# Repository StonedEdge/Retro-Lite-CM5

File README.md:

<div align="center">
  <h1>Retro Lite/RetrOLED CM5: RK3588s Gaming Handheld</h1>
</div>

<div align="center">
  
</div>
<p align="center">This is the RetroLED CM5, a handheld console designed by GinKage, notime2d8 and StonedEdge.</p>

<div align="center">
  
</div>
<p align="center">Running Hollow Knight via Box64 and Steam on upstream Armbian kernel.</p>

<div align="center">
  
</div>
<p align="center">Official Android support, thanks to the work of notime2d8.</p>

<div align="center">
  
</div>
<p align="center">Latest ROCKNIX images available with Vulkan driver support.</p>

<div align="center">
  
</div>
<p align="center">Open source hardware files available for download.</p>

The Retro Lite/RetrOLED CM5 is an upgrade to the Retro Lite CM4 handheld. The project goal is to create a more powerful handheld that can handle 3DS, PS2 and GC emulation (none of which the Pi can do). I also would like to be able to play some games via Box64/86. It has a relatively large battery so run time should be excellent, considering it is ARM based. **Now with an optional OLED upgrade!**

Powered by the RK3588s compute module from Radxa, which is an SBC SOM module with an ARMv8 64-bit processor. Features 8 cores/threads - 4 x ARM Cortex-A55/A76 cores with A55 cores clocked at 1.8GHz, and A76 cores clocked at 2.4GHz. It also has a built-in Mali G610 GPU. 

The Retro Lite/RetrOLED CM5 offers a more modern gaming experience with DisplayPort via USB Type-C, USB 3.0 & HDMI 2.1. Built-in PCIe WiFI 6.0 & BT 5.2, as well as a new 720p IPS display @ 5.5" with touchscreen support & dual tact trigger buttons for GameCube support, make this a much more viable low-powered ARM SBC gaming PC than the Raspberry Pi 4. 

The operating system will be based on Armbian, with a custom device tree for hardware interfacing & RetroPie pre-installed. However, the user can use it however they would like, either in a Linux desktop environment or with other Linux based frontends, such as ES-DE. This handheld should be able to play the entire PS2 library at least 1x native resolution for all games, as well as GameCube at 1x on Linux with OpenGLES drivers. Android is currently more performant due to Vulkan drivers, however Linux Vulkan blobs should come soon (or someday, who knows). We also now have succesfully compiled ROCKNIX as well. Eventually I will compile all of the final images to GitHub. 

For regular updates/following progress on the build, please check out the forum post here:
https://bitbuilt.net/forums/index.php?threads/retro-lite-cm5.5815/

# Retro Lite/RetrOLED CM5: Radxa RK3588s Handheld 

## Features

Hardware specifications:

- 3D printable housing in PLA. Comfort grips for added ergonomics
- Radxa CM5 Compute Module (8GB RAM/64GB eMMC)
- SoC – Rockchip RK3588S octa-core processor with 4x Cortex‑A76 cores @ up to 2.4GHz, 4x Cortex‑A55 core @ 1.8GHz
Arm Mali-G610 MP4 “Odin” GPU Video decoder – 8Kp60 H.265, VP9, AVS2, 8Kp30 H.264 AVC/MVC, 4Kp60 AV1, 1080p60 MPEG-2/-1, VC-1, VP8 Video encoder – 8Kp30 H.265/H.264 video encoder
- WiFi 6/Bluetooth 5.2 via PCIe E-key slot (Intel AX210) - https://www.intel.com/content/www/us/en/products/sku/204836/intel-wifi-6e-ax210-gig/specifications.html
- 6 layer carrier board with 3 B2B mezzanine connectors to interface with any Radxa CM5 module 
- 5v boost rated at 3.5A continuous current
- RP2040 gamepad - complete with SDL mappings and evdev gyro support/mouse control via MPU6050
- 1280 x 720p (5.5" DSI IPS LCD): DSI video output on internal display
**- New: Optional 1920 x 1080p (5.44" AMOLED): DSI video output on internal display** 
- Up to 4k HDMI video output via HDMI output
- Up to 4k DisplayPort Alternate Mode via Type-C
- USB 2.0/3.1 capable USB-C data transfer
- USB-C dual role port functionality (sink/source)
- Brightness and volume HUD adjustment. Brightness is adjusted by holding plus hotkey + down/up. Volume controlled either by volume buttons or plus hotkey + left right DPAD
- USB-C PD charging support via sink profiles supporting 5V/3A, 9V/3A, 12V/2A & 15V/2.6A (switch charger) via TPS65987D PD controller (see binary in TPS65987D folder). Recommended to use <12V for best charge and play performance 
- Stereo Audio Output via i2s. Dual stereo speakers with ported chambers
- Headphone jack, with automatic switching
- 5000mAh lipo, providing around 1.5-5 hours of gameplay depending on load (to be upgraded soon to >8000mAh)
- Dual stacked shoulder buttons (L, R, LZ, RZ) with dual tact buttons for GameCube functionality (LR analog/LR digital)
- 2x hall effect analog sticks running at 3v3
- Resin casted ABXY, DPAD, start+select, shoulder buttons
- Silicone membranes for nice button feel 

Software specifications:

- Armbian GNOME desktop (Kernel 6.1.57 as of this post)
- Android 13 support (beta)
- Full upstream Rocknix support
- Wayland windowing system (xorg capable)
- Hardware graphics support via Panfrost/OpenGLES/I want a broken vulkan driver "support"
- Safe software/hardware shutdown (either from software or via button)
- Low power sleep mode - in my tests, 24 hours in standby mode draws around 6% of total battery life
- Range adjustable joysticks in software by pressing plus hotkey plus R3 --> A --> rotate sticks --> A combination
-------------------------------------------------------------------------------------------------------

### CAD
Enclosure files have been uploaded in STL and STEP format [here.](https://github.com/StonedEdge/Retro-Lite-CM5/tree/main/enclosure)
Make sure to use v2 as these contain all the latest and greatest changes. 

-------------------------------------------------------------------------------------------------------

### PCB
v1 Controller PCBs have been uploaded [here.](https://github.com/StonedEdge/Retro-Lite-CM5/tree/main/rp2040_gamepad/PCB)
Please note that you will not be able to assemble the unit with the UART/serial debug components soldered onto the boards, so make sure these aren't populated. 

v1.1 CM5 carrier boards have been uploaded [here.](https://github.com/StonedEdge/Retro-Lite-CM5/tree/main/cm5_carrier_pcb)

-------------------------------------------------------------------------------------------------------

### BOM (Bill of Materials) 
v1 Right Controller PCB BOM have been uploaded [here.](https://github.com/StonedEdge/Retro-Lite-CM5/blob/main/rp2040_gamepad/PCB/Retro_Lite_CM5_Right_PCB_v1%20-%20BOM.csv)

v1 Left Controller PCB BOM have been uploaded [here.](https://github.com/StonedEdge/Retro-Lite-CM5/blob/main/rp2040_gamepad/PCB/v1/Retro_Lite_CM5_Left_PCB_v1%20-%20BOM.csv)

v1 V2.2 Carrier PCB BOM has been uploaded [here.](https://github.com/StonedEdge/Retro-Lite-CM5/blob/main/cm5_carrier_pcb/Retro_Lite_CM5_IO_X2.2_BOM.csv) 
The board has been verified and fully functional with Radxa V2.2 CM5 modules! V2.21 also works fine. 

-------------------------------------------------------------------------------------------------------

### To-do
- [x] Hardware familiarization - Orange Pi 5/Radxa CM5/IO board schematics
- [x] Design v1 prototype left/right controller PCBs (ATMEGA32u4 based)
- [x] Design v1 DSI test display board
- [x] Design v1 Power Management/DisplayPort/USB-C PD test board
- [x] Order v1 Power Management/DisplayPort/USB-C PD test board
- [x] Design v2 prototype left/right controller PCBs (RP2040 based)
- [x] Test v1 Power Management/DisplayPort Alternate Mode/USB-C PD test board functionality - works!
- [x] Design CM5 carrier main board (v1.0) that implements new hardware features, such as DisplayPort, USB3 and PCIe
- [x] Order CM5 carrier board (v1.0) with desired fab house. (It's in production!)
- [x] Test CM5 carrier board (v1.0) hardware for a basic functioning prototype
- [x] Redesign CM5 carrier board (v1.1) with fixes for 3rd connector polarity & other small fixes
- [x] Reorder v1.1 carrier board
- [x] Investigate RK806 PMIC issue
- [x] Prepare an Armbian based OS image, including the BSP (bootloader, dtb and kernel) for the RK3588s Armbian rootfs. DTB should include the ILI9881C/WM8960 drivers
- [x] Integrate new 5.5 inch MIPI DSI display. This includes enabling the ILI9881C display driver, device tree customizations for the display
- [x] Test and verify display functionality, including proper backlight & 60 FPS. Verify display works with Armbian 
- [x] WM8960 codec integration via Orange Pi 5/CM5 IO for testing. Integrate the WM8960 i2c code driver including any device tree customizations for codec. Finally, test and verify audio works correctly
- [x] Integrate touch/verify via the GT911 controller 
- [x] Test and verify emulators work correctly with Mali blobs and can be launched via EmulationStation front end
- [x] Setup Mali Open GL blob drivers to work with PS2 (AetherSX2) & GC (Dolphin) emulators due to no Vulkan backend available (yet!)
- [x] Write HID controller code for RP2040. Verify basic gamepad functionality works as intended
- [x] Integrate an IMU into the controller PCB for gyro functionality. Include EKF algorithm (MPU-6050 6-axis IMU) 
- [x] Redesign housing (increase 3mm in all directions) in Solidworks. Improve trigger feel and add battery mounting bracket
- [x] Redesign housing v2 (increase thickness to accomodate 6Ah battery cell at 3.8v, mount battery and fan to front housing)
- [x] Redesign housing with injection molding in mind - include appropriate draft angles, ribs, gussets, radiused corners & bosses
- [x] Redesign housing to use original switch lite fan enclosure 
- [x] Power on/power off/sleep mode via ATtiny84 (Power control)
- [x] Put together a fully functional dts for the CM5 IO Board (Device Tree Source) to understand hardware configuration 
- [x] MAX17055 integration into device tree 
- [x] Prepare reference implementation for launching games via EmulationStation/some form of frontend (likely ES-DE/RetroPie)
- [x] Implement an on-screen indicator for volume, brightness control via GPIOs
- [x] Rocknix upstream support
- [x] Android 13 support 
- [ ] Adjust BQ24292i registers to charge to 4.35v max instead of 4.2v due to using LiHv cell (might not do, given cells may go kaboom)
- [x] Other optimizations/improvements/bug fixes
- [x] Create prototype showcase video for YouTube
- [x] Final GitHub open source release & announcement!
- [x] Integrate OLED RM67199 patches
- [x] Integrate goodix gtx8 patches (GT9886)
-------------------------------------------------------------------------------------------------------

### Firmware 
At the moment, there are a couple of options for firmware which I will separate out into two devices, the Retro Lite CM5 and the RetrOLED CM5. 
We are continuing to work on these - few developers will be getting units soon which should accelerate the process of development as well.  

**Retro Lite CM5**
- [x] ROCKNIX
- [x] Armbian Gnome Desktop (OpenGL/OpenGLES)
- [x] Armbian Gnome Desktop (OpenGLES/Vulkan)
- [x] Android 13 (Beta)
- [ ] Android 14 (kind of lost interest in Android, probably not likely to happen anytime soon). 

**RetrOLED CM5**
- [x] ROCKNIX
- [x] Armbian Gnome Desktop (OpenGL/OpenGLES)
- [x] Armbian Gnome Desktop (OpenGLES/Vulkan)
- [ ] Android 13 (Beta - shit is broken, like brightness control which we never got working)
- [ ] Android 14 (kind of lost interest in Android, probably not likely to happen anytime soon). 
-------------------------------------------------------------------------------------------------------

### Frequently Asked Questions (FAQ) 
Q: How can I get my hand on a Retro Lite/RetrOLED CM5? Do you sell them or will you sell them?

A: Radxa have advised that **this device will not be mass produced**. There is no method to get your hands on one of these at this time. This project is mainly for fun, cost is not a huge consideration here. 

Q: How much does it cost in parts to build one of these?

A: Expect to spend at minimum around $350-400 for a single one-off build. 

Q: Why dont you use an OLED screen? 

A: **Funny you ask. We now have OLED support!** The OLED screen is functioning with touch integration. We are using this OLED screen here: https://www.alibaba.com/product-detail/oled-display-module-5-44inch-oled_60726980273.html
Make sure you confirm the model number is ET055FH06-GT. You will also need to order the flex PCB with JLCPCB (costs around $10). 2 layer is fine, make sure to send them the production files as a reference. I have verified that it works with the current carrier board. 

Q: Why do this when you can get an equivalent handheld from Aliexpress for $150? This is stupid and DOA! Makes no sense! Non-sensical! I'm going to buy myself a better handheld. 

A: Because it's fun to build something awesome. It's not about the end result, its the process for me. Thanks for visiting & farewell, this project probably isn't for you. 

Q: Is Vulkan working yet on Linux?

A: We have a temporarily solution for Vulkan on Linux, but the driver is not conformant yet. PanVk is on its way though. 

Q: Can you please make me one for exposure on YouTube? I promise to give incredible reviews!

A: Nope. I simply don't have time. Sorry. 

### License

[![CC BY-NC-SA 4.0][cc-by-nc-sa-shield]][cc-by-nc-sa]

This work is licensed under a
[Creative Commons Attribution-NonCommercial-ShareAlike 4.0 International License][cc-by-nc-sa].

[![CC BY-NC-SA 4.0][cc-by-nc-sa-image]][cc-by-nc-sa]

[cc-by-nc-sa]: http://creativecommons.org/licenses/by-nc-sa/4.0/
[cc-by-nc-sa-image]: https://licensebuttons.net/l/by-nc-sa/4.0/88x31.png
[cc-by-nc-sa-shield]: https://img.shields.io/badge/License-CC%20BY--NC--SA%204.0-lightgrey.svg

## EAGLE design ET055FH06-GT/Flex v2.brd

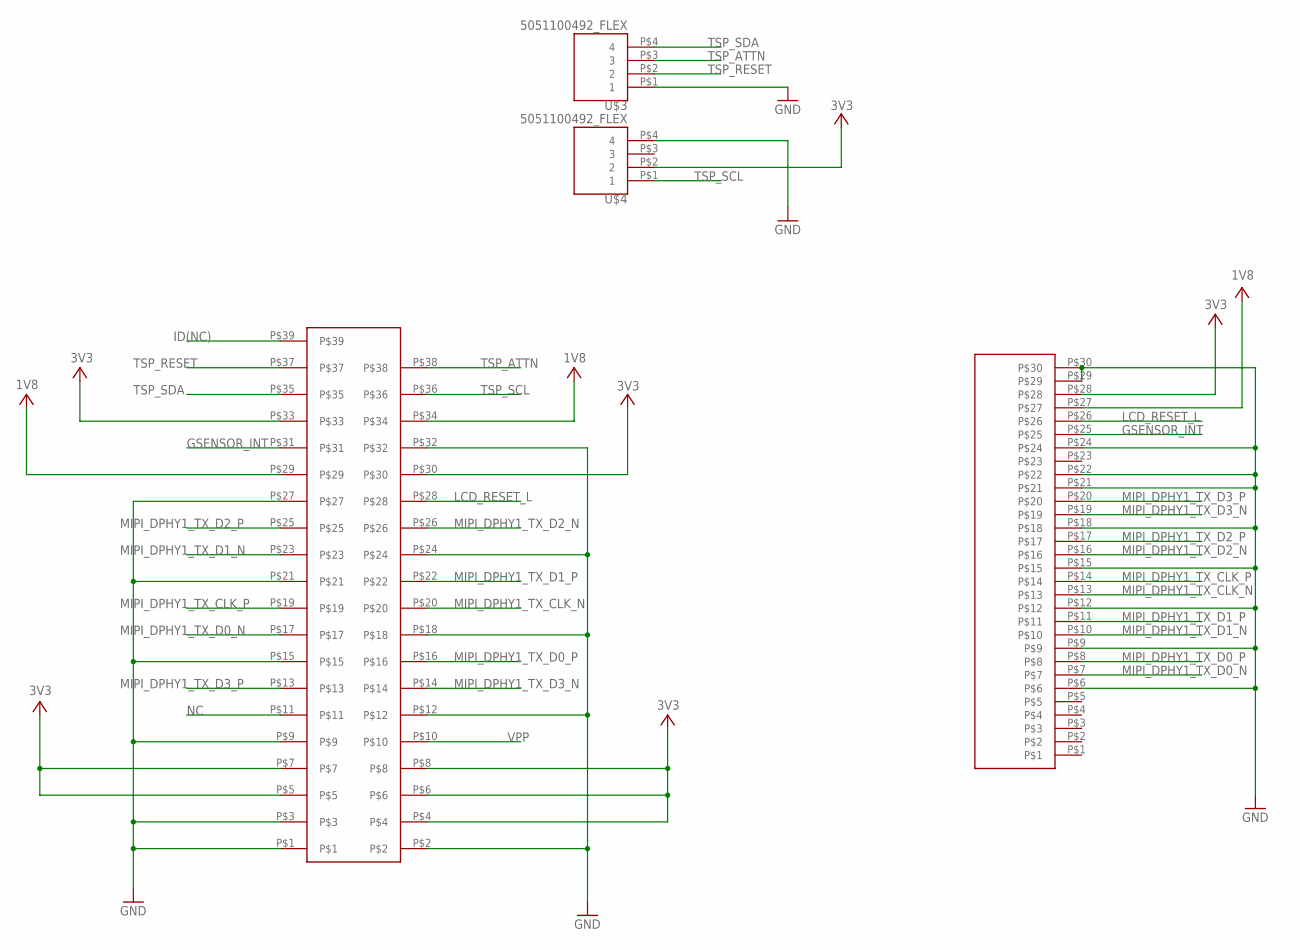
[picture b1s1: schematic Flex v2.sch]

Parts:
U$1: FH26-39S-0.3SHW_FLEX
U$2: 5051103091
U$3, U$4: 5051100492_FLEX

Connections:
1V8: U$1.P$29, U$1.P$34, U$2.P$27
3V3: U$1.P$4, U$1.P$5, U$1.P$6, U$1.P$7, U$1.P$8, U$1.P$30, U$1.P$33, U$2.P$28, U$4.P$2 (2)
GND: U$1.P$1, U$1.P$2, U$1.P$3, U$1.P$9, U$1.P$12, U$1.P$15, U$1.P$18, U$1.P$21, U$1.P$24, U$1.P$27, U$1.P$32, U$2.P$6, U$2.P$9, U$2.P$12, U$2.P$15, U$2.P$18, U$2.P$21, U$2.P$22, U$2.P$24, U$2.P$29, U$2.P$30, U$3.P$1 (1), U$4.P$4 (4)
GSENSOR_INT: U$1.P$31, U$2.P$25
ID(NC): U$1.P$39
LCD_RESET_L: U$1.P$28, U$2.P$26
MIPI_DPHY1_TX_CLK_N: U$1.P$20, U$2.P$13
MIPI_DPHY1_TX_CLK_P: U$1.P$19, U$2.P$14
MIPI_DPHY1_TX_D0_N: U$1.P$17, U$2.P$7
MIPI_DPHY1_TX_D0_P: U$1.P$16, U$2.P$8
MIPI_DPHY1_TX_D1_N: U$1.P$23, U$2.P$10
MIPI_DPHY1_TX_D1_P: U$1.P$22, U$2.P$11
MIPI_DPHY1_TX_D2_N: U$1.P$26, U$2.P$16
MIPI_DPHY1_TX_D2_P: U$1.P$25, U$2.P$17
MIPI_DPHY1_TX_D3_N: U$1.P$14, U$2.P$19
MIPI_DPHY1_TX_D3_P: U$1.P$13, U$2.P$20
NC: U$1.P$11
TSP_ATTN: U$1.P$38, U$3.P$3 (3)
TSP_RESET: U$1.P$37, U$3.P$2 (2)
TSP_SCL: U$1.P$36, U$4.P$1 (1)
TSP_SDA: U$1.P$35, U$3.P$4 (4)
VPP: U$1.P$10

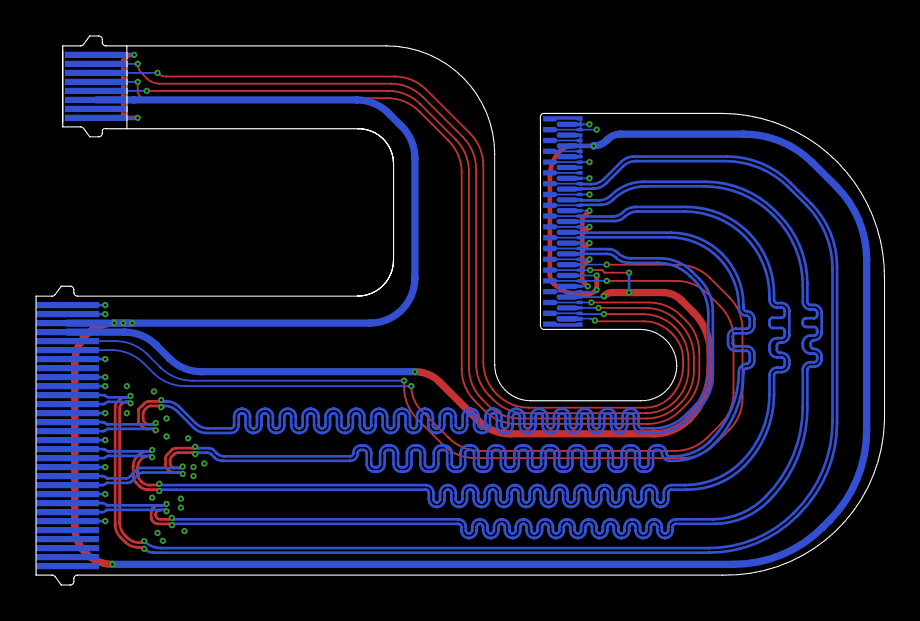
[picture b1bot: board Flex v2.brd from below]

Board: 2 copper layers, 47.1 x 30.5 mm, 4 parts (4 on the bottom side), 19 nets.

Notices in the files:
parts and their libraries:
COPYRIGHT: Copyright (C) 2023 Ultra Librarian. All rights reserved.
SparkFun-Capacitors: Licensing: Creative Commons ShareAlike 4.0 International - https://creativecommons.org/licenses/by-sa/4.0
Eagle_WA-SMSI: Copyright: Würth Elektronik
